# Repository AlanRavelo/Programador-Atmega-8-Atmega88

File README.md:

# Programador-Atmega-8 / Atmega 88
Dispositivo para cargar el programa en el microcontrolador ATmega8 - atmega88p.

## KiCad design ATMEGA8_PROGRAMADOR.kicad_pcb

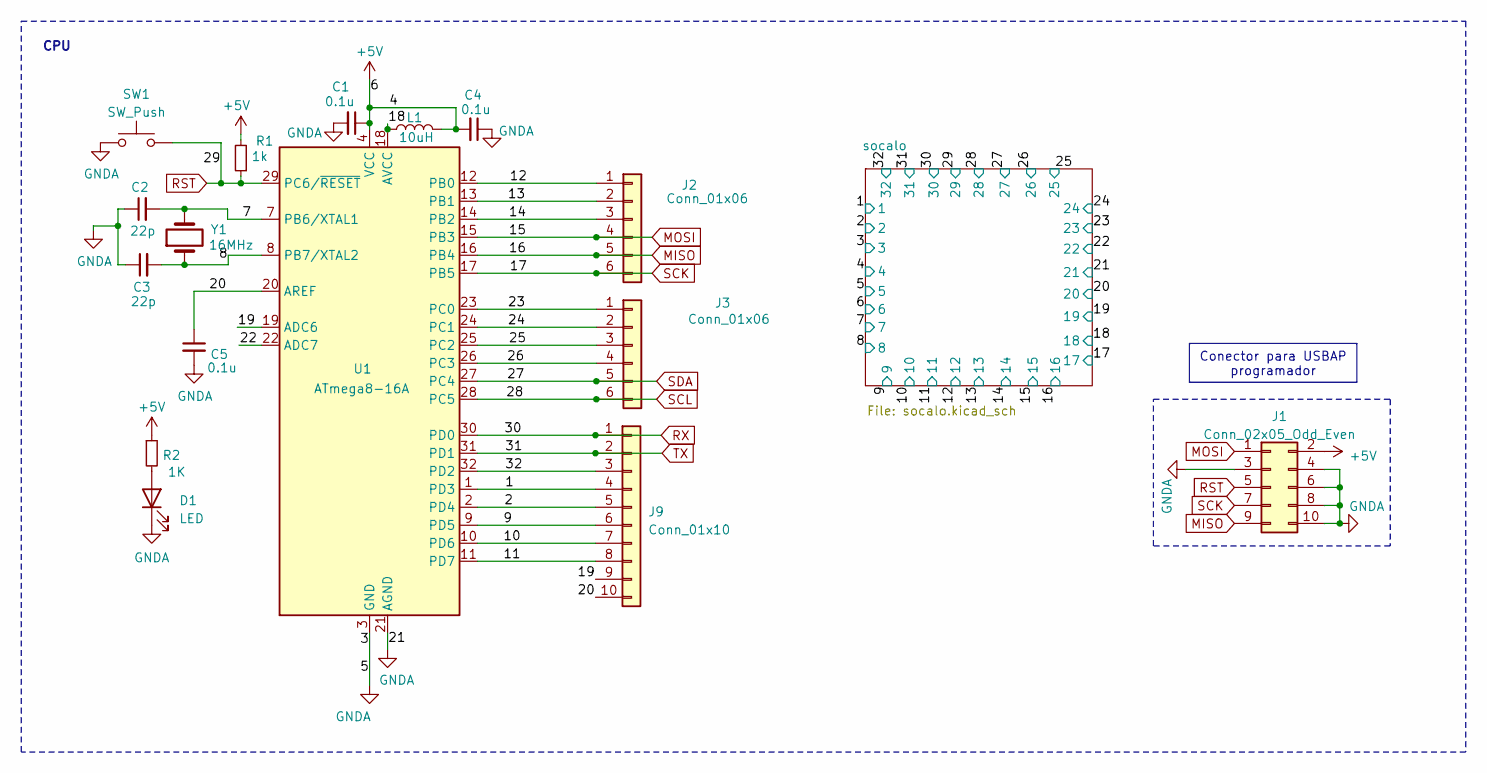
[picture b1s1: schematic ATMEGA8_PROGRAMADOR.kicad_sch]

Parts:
C1: 0.1u; C_Disc_D3.0mm_W1.6mm_P2.50mm
C2, C3: 22p; C_Disc_D3.0mm_W2.0mm_P2.50mm
C4, C5: 0.1u; C_Disc_D3.0mm_W2.0mm_P2.50mm
D1: LED; LED_D3.0mm
J1: Conn_02x05_Odd_Even; PinHeader_2x05_P2.54mm_Vertical
J2, J3: Conn_01x06; PinHeader_1x06_P2.54mm_Vertical
J9: Conn_01x10; PinSocket_1x10_P2.54mm_Vertical
L1: 10uH; L_Axial_L5.0mm_D3.6mm_P10.00mm_Horizontal_Murata_BL01RN1A2A2
R1: 1k; R_Axial_DIN0204_L3.6mm_D1.6mm_P5.08mm_Horizontal
R2: 1K; R_Axial_DIN0204_L3.6mm_D1.6mm_P5.08mm_Horizontal
SW1: SW_Push; SW_PUSH_6mm
U1: ATmega8-16A; TQFP-32_7x7mm_P0.8mm
Y1: 16MHz; Crystal_HC18-U_Vertical

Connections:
+5V: C1.1, C4.2, J1.2, L1.2, R1.2, R2.1, U1.4 (VCC), U1.6 (VCC); also elsewhere on the board
/1: J9.4, U1.1 (PD3); also elsewhere on the board
/2: J9.5, U1.2 (PD4); also elsewhere on the board
/7: C2.2, U1.7 (PB6/XTAL1), Y1.2; also elsewhere on the board
/8: C3.2, U1.8 (PB7/XTAL2), Y1.1; also elsewhere on the board
/9: J9.6, U1.9 (PD5); also elsewhere on the board
/10: J9.7, U1.10 (PD6); also elsewhere on the board
/11: J9.8, U1.11 (PD7); also elsewhere on the board
/12: J2.1, U1.12 (PB0); also elsewhere on the board
/13: J2.2, U1.13 (PB1); also elsewhere on the board
/14: J2.3, U1.14 (PB2); also elsewhere on the board
/18: L1.1, U1.18 (AVCC); also elsewhere on the board
/19: J9.9, U1.19 (ADC6); also elsewhere on the board
/20: C5.1, J9.10, U1.20 (AREF); also elsewhere on the board
/22: U1.22 (ADC7); also elsewhere on the board
/23: J3.1, U1.23 (PC0); also elsewhere on the board
/24: J3.2, U1.24 (PC1); also elsewhere on the board
/25: J3.3, U1.25 (PC2); also elsewhere on the board
/26: J3.4, U1.26 (PC3); also elsewhere on the board
/32: J9.3, U1.32 (PD2); also elsewhere on the board
GND: C1.2, C2.1, C3.1, C4.1, C5.2, D1.1 (K), J1.3, J1.4, J1.6, J1.8, J1.10, SW1.1, U1.3 (GND), U1.5 (GND), U1.21 (AGND); also elsewhere on the board
MISO: J1.9, J2.5, U1.16 (PB4); also elsewhere on the board
MOSI: J1.1, J2.4, U1.15 (PB3); also elsewhere on the board
unnamed: D1.2 (A), R2.2
RST: J1.5, R1.1, SW1.2, U1.29 (PC6/~RESET); also elsewhere on the board
RX: J9.1, U1.30 (PD0); also elsewhere on the board
SCK: J1.7, J2.6, U1.17 (PB5); also elsewhere on the board
SCL: J3.6, U1.28 (PC5); also elsewhere on the board
SDA: J3.5, U1.27 (PC4); also elsewhere on the board
TX: J9.2, U1.31 (PD1); also elsewhere on the board

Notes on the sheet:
Conector para USBAP programador
CPU

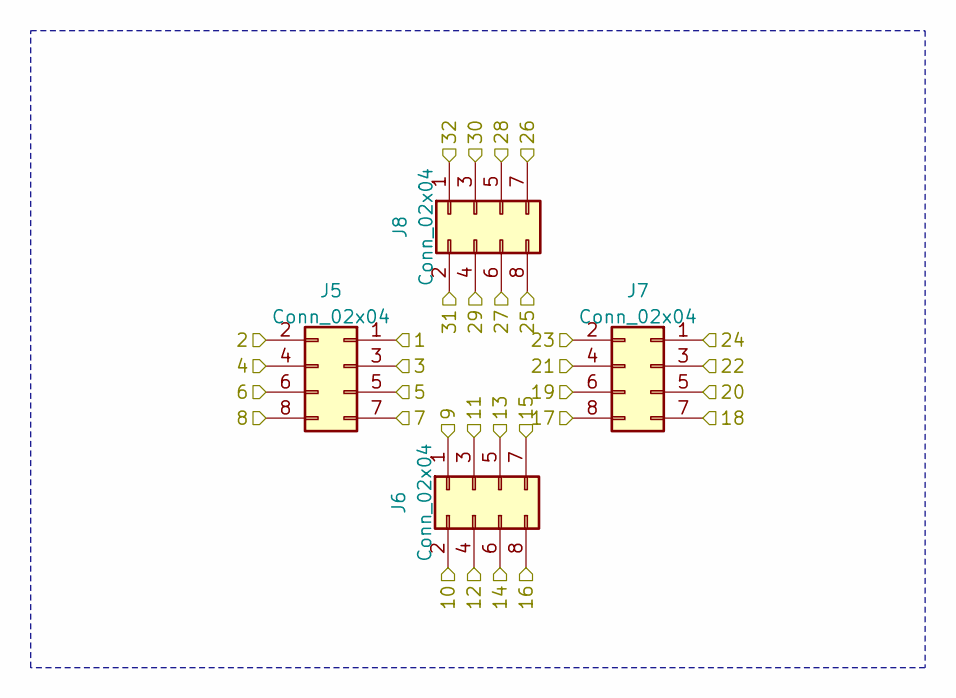
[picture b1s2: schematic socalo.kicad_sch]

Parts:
J5, J6, J7, J8: Conn_02x04; PinHeader_2x04_P2.54mm_Vertical; Part Number 1-0802FBV0T

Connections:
+5V: J6.4, J6.6; also elsewhere on the board
/1: J6.1; also elsewhere on the board
/2: J6.2; also elsewhere on the board
/7: J6.7; also elsewhere on the board
/8: J6.8; also elsewhere on the board
/9: J8.1; also elsewhere on the board
/10: J8.2; also elsewhere on the board
/11: J8.3; also elsewhere on the board
/12: J8.4; also elsewhere on the board
/13: J8.5; also elsewhere on the board
/14: J8.6; also elsewhere on the board
/18: J7.7; also elsewhere on the board
/19: J7.6; also elsewhere on the board
/20: J7.5; also elsewhere on the board
/22: J7.3; also elsewhere on the board
/23: J7.2; also elsewhere on the board
/24: J7.1; also elsewhere on the board
/25: J5.8; also elsewhere on the board
/26: J5.7; also elsewhere on the board
/32: J5.1; also elsewhere on the board
GND: J6.3, J6.5, J7.4; also elsewhere on the board
MISO: J8.8; also elsewhere on the board
MOSI: J8.7; also elsewhere on the board
RST: J5.4; also elsewhere on the board
RX: J5.3; also elsewhere on the board
SCK: J7.8; also elsewhere on the board
SCL: J5.5; also elsewhere on the board
SDA: J5.6; also elsewhere on the board
TX: J5.2; also elsewhere on the board

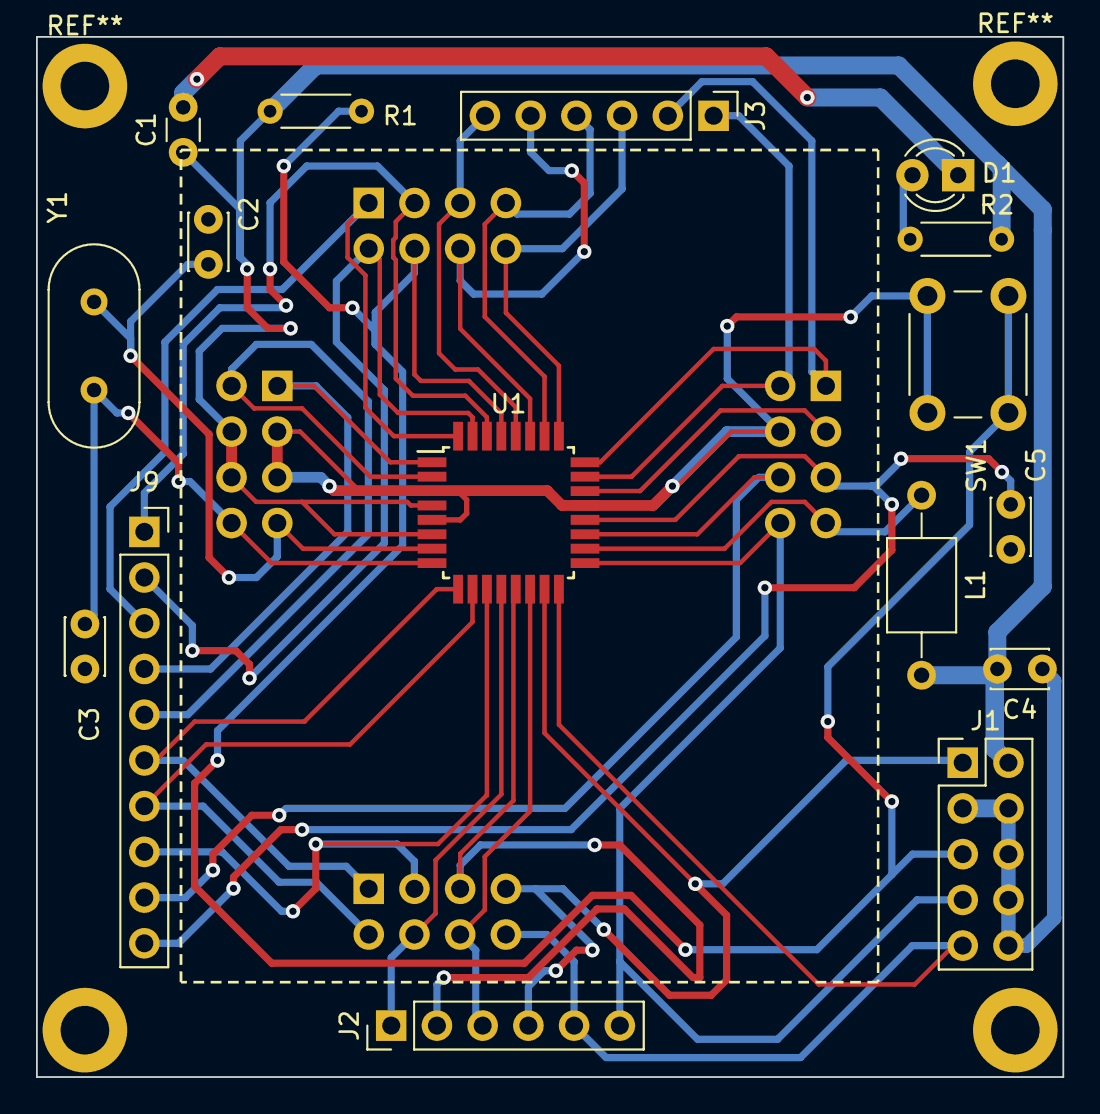
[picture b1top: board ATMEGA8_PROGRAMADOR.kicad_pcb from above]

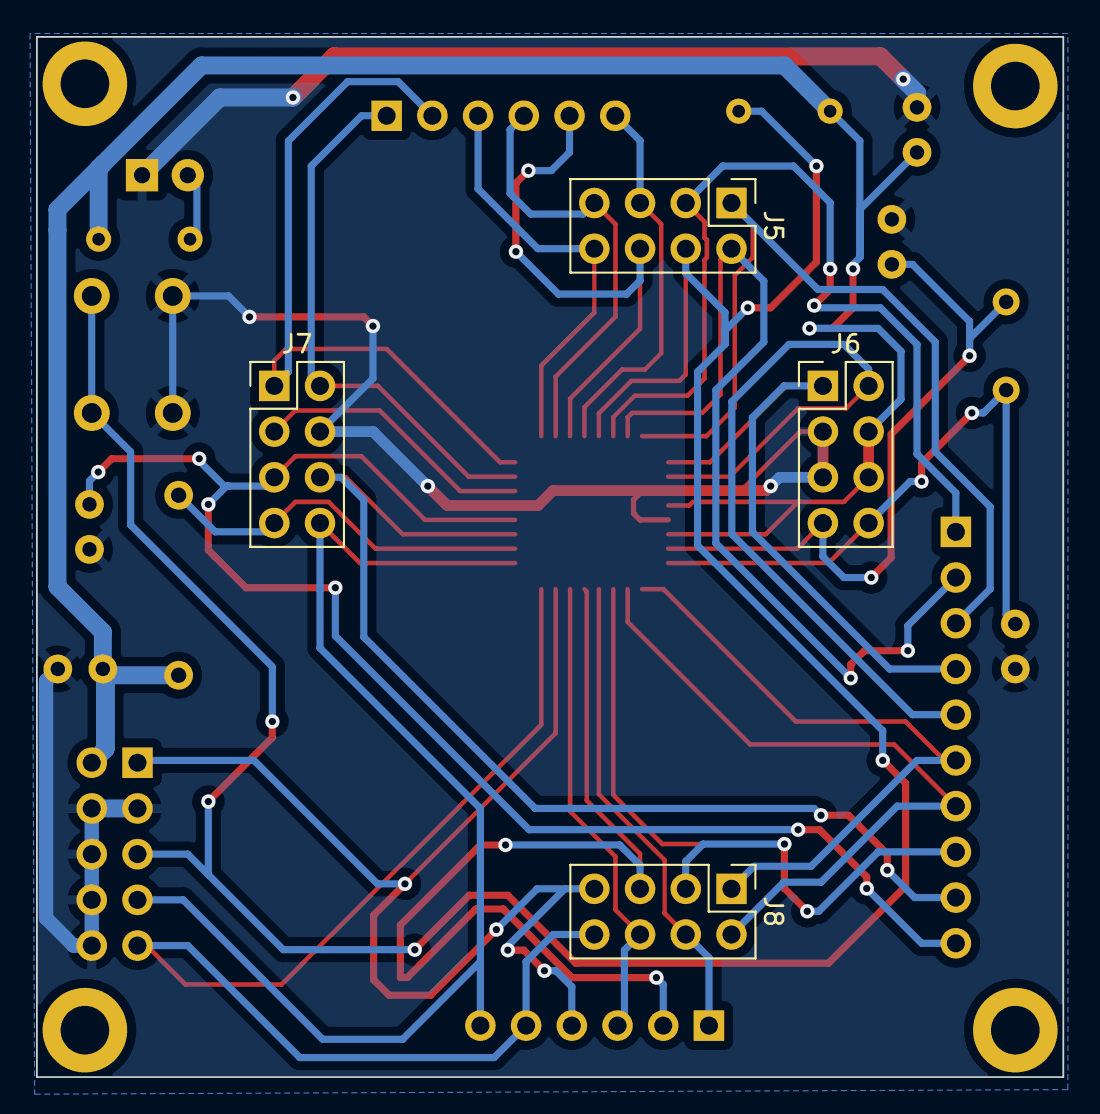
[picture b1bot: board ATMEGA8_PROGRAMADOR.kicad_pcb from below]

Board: 2 copper layers, 57.0 x 57.8 mm, 20 parts (4 on the bottom side), 30 nets.
